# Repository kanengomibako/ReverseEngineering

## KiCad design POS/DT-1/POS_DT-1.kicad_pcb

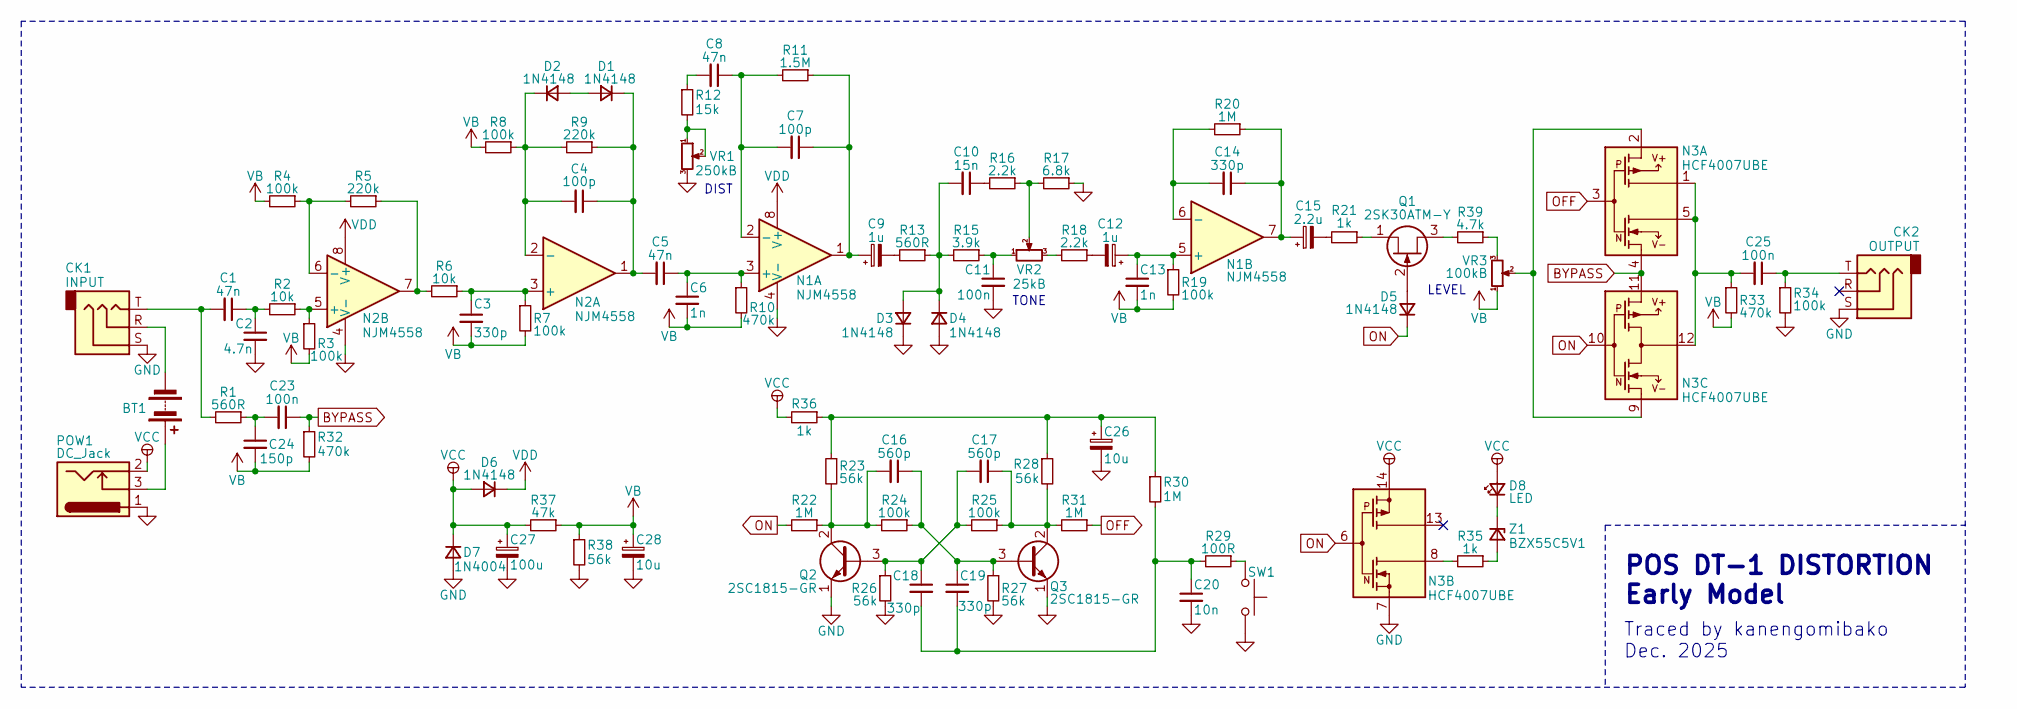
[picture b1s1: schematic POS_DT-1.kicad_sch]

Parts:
BT1: 006P; my_conn
C1, C5, C8: 47n; my_C_Rect1_P5.00mm
C2: 4.7n; my_C_Rect1_P5.00mm
C3, C14, C18, C19: 330p; my_C_Rect1_P5.00mm
C4, C7: 100p; my_C_Rect1_P5.00mm
C6, C13: 1n; my_C_Rect1_P5.00mm
C9, C12: 1u; my_C_D5.0mm_P2.50mm
C10: 15n; my_C_Rect1_P5.00mm
C11, C23, C25: 100n; my_C_Rect1_P5.00mm
C15: 2.2u; my_C_D5.0mm_P2.50mm
C16, C17: 560p; my_C_Rect1_P5.00mm
C20: 10n; my_C_Rect1_P5.00mm
C24: 150p; my_C_Rect1_P5.00mm
C26, C28: 10u; my_C_D5.0mm_P2.50mm
C27: 100u; my_C_D5.0mm_P2.50mm
CK1: INPUT; Audio_Jack_EX
CK2: OUTPUT; Audio_Jack_EX
D1, D2, D3, D4, D5, D6: 1N4148; my_D_P5.08mm_Horizontal
D7: 1N4004; my_D_P7.62mm
D8: LED; my_conn
N1, N2: NJM4558; DIP-8_W7.62mm
N3: HCF4007UBE; DIP-14_W7.62mm
POW1: DC_Jack; my_DC_Jack
Q1: 2SK30ATM-Y; TO-92_Inline_Wide
Q2, Q3: 2SC1815-GR; TO-92_Inline_Wide
R1: 560R; my_R_P5.08mm_Horizontal
R2, R6: 10k; my_R_P5.08mm_Horizontal
R3, R4, R7, R8, R19, R24, R25, R34: 100k; my_R_P5.08mm_Horizontal
R5, R9: 220k; my_R_P5.08mm_Horizontal
R10, R32, R33: 470k; my_R_P5.08mm_Horizontal
R11: 1.5M; my_R_P5.08mm_Horizontal
R12: 15k; my_R_P5.08mm_Horizontal
R13: 560R; my_R_P10mm_Horizontal
R15: 3.9k; my_R_P5.08mm_Horizontal
R16, R18: 2.2k; my_R_P5.08mm_Horizontal
R17: 6.8k; my_R_P5.08mm_Horizontal
R20, R30: 1M; my_R_P5.08mm_Horizontal
R21, R35, R36: 1k; my_R_P5.08mm_Horizontal
R22, R31: 1M; my_R_P10mm_Horizontal
R23: 56k; my_R_P10mm_Horizontal
R26, R27, R28, R38: 56k; my_R_P5.08mm_Horizontal
R29: 100R; my_R_P10mm_Horizontal
R37: 47k; my_R_P5.08mm_Horizontal
R39: 4.7k; my_R_P5.08mm_Horizontal
SW1: SW_Push; my_conn
VR1: 250kB; PinHeader_1x03_P2.54mm_Vertical
VR2: 25kB; PinHeader_1x03_P2.54mm_Vertical
VR3: 100kB; PinHeader_1x03_P2.54mm_Vertical
Z1: BZX55C5V1; my_D_P7.62mm

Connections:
BYPASS: C23.1, N3.4, N3.11, R32.1
GND: C2.2, C11.2, C20.2, C26.2, C27.2, C28.2, CK1.S, CK2.S, D3.1 (K), D4.2 (A), D7.2 (A), N1.4 (V-), N2.4 (V-), N3.7, POW1.1, Q2.1 (E), Q3.1 (E), R17.1, R26.2, R27.2, R34.2, R38.2, SW1.2, VR1.3
unnamed: BT1.1 (+), POW1.3
unnamed: BT1.2 (-), CK1.R
unnamed: C1.1, C2.1, R2.2
unnamed: C1.2, CK1.T, R1.2
unnamed: C7.1, C9.1, N1.1, R11.1
unnamed: C8.2, R12.1
unnamed: C9.2, R13.2
unnamed: C10.1, R16.2
unnamed: C11.1, R15.1, VR2.1
unnamed: C12.2, R18.1
unnamed: C14.1, C15.1, N1.7, R20.1
unnamed: C15.2, R21.2
unnamed: C18.2, C19.2, C20.1, R29.2, R30.2
unnamed: C23.2, C24.1, R1.1
unnamed: C25.1, CK2.T, R34.1
unnamed: C25.2, N3.1, N3.5, N3.12, R33.1
unnamed: C26.1, R23.1, R28.1, R30.1, R36.1
unnamed: D1.2 (A), D2.2 (A)
unnamed: C4.1, C5.2, D1.1 (K), N2.1, R9.1
unnamed: C4.2, D2.1 (K), N2.2 (-), R8.1, R9.2
unnamed: C10.2, D3.2 (A), D4.1 (K), R13.1, R15.2
unnamed: D5.2 (A), Q1.2 (G)
unnamed: D8.1 (K), Z1.1 (K)
unnamed: C5.1, C6.1, N1.3 (+), R10.1
unnamed: C7.2, C8.1, N1.2 (-), R11.2
unnamed: C12.1, C13.1, N1.5 (+), R19.1
unnamed: C14.2, N1.6 (-), R20.2
unnamed: N2.7, R5.1, R6.2
unnamed: C3.1, N2.3 (+), R6.1, R7.1
unnamed: N2.5 (+), R2.1, R3.1
unnamed: N2.6 (-), R4.1, R5.2
unnamed: N3.2, N3.9, VR3.2
unnamed: N3.8, R35.2
unnamed: Q1.3 (D), R39.2
unnamed: Q1.1 (S), R21.1
unnamed: C17.2, C18.1, Q2.3 (B), R25.2, R26.1
unnamed: C16.2, Q2.2 (C), R22.1, R23.2, R24.2
unnamed: C16.1, C19.1, Q3.3 (B), R24.1, R27.1
unnamed: C17.1, Q3.2 (C), R25.1, R28.2, R31.2
unnamed: R12.2, VR1.1, VR1.2
unnamed: R16.1, R17.2, VR2.2
unnamed: R18.2, VR2.3
unnamed: R29.1, SW1.1
unnamed: R39.1, VR3.3
unnamed: R35.1, Z1.2 (A)
OFF: N3.3, R31.1
ON: D5.1 (K), N3.6, N3.10, R22.2
VB: C3.2, C6.2, C13.2, C24.2, C28.1, R3.2, R4.2, R7.2, R8.2, R10.2, R19.2, R32.2, R33.2, R37.1, R38.1, VR3.1
VCC: C27.1, D6.2 (A), D7.1 (K), D8.2 (A), N3.14, POW1.2, R36.2, R37.2
VDD: D6.1 (K), N1.8 (V+), N2.8 (V+)

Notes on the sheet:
TONE
POS DT-1 DISTORTION Early Model
LEVEL
Traced by kanengomibako Dec. 2025
DIST

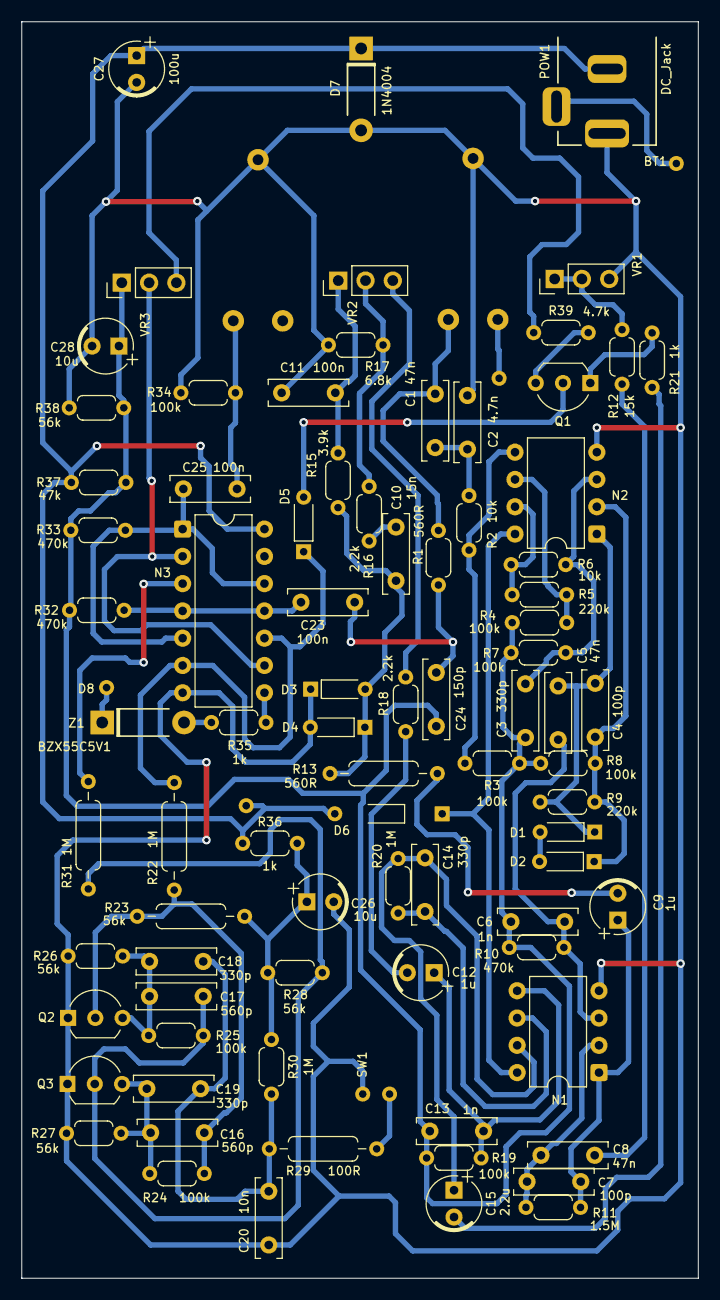
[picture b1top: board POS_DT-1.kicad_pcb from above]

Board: 2 copper layers, 63.0 x 117.0 mm, 87 parts (0 on the bottom side), 52 nets.

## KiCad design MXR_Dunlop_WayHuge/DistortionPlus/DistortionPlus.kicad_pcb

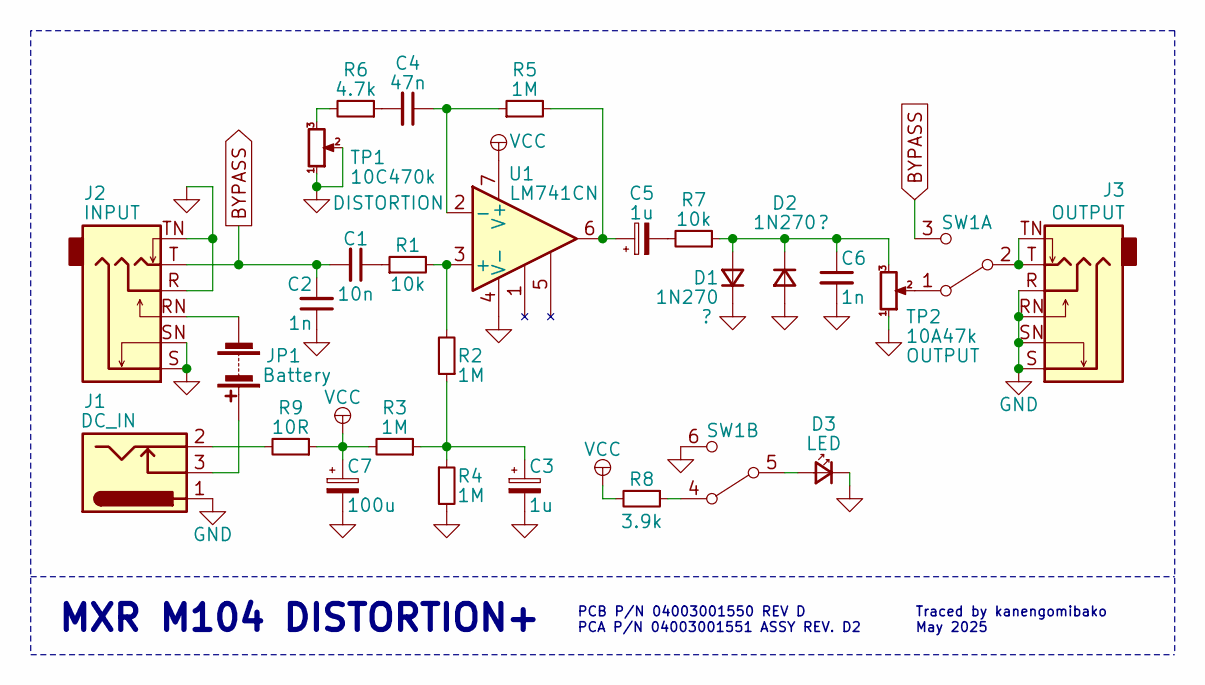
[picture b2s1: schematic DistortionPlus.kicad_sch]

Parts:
C1: 10n; my_C_Rect1_P5.00mm
C2, C6: 1n; my_C_Rect1_P5.00mm
C3, C5: 1u; CP_Radial_D5.0mm_P2.50mm
C4: 47n; my_C_Rect1_P5.00mm
C7: 100u; CP_Radial_D5.0mm_P2.50mm
D1, D2: 1N270; D_A-405_P10.16mm_Horizontal
D3: LED; LED_D3.0mm
J1: DC_IN; my_DC_Jack
J2: INPUT; Jack_6.35mm_Neutrik_NMJ6HCD2_Horizontal
J3: OUTPUT; Jack_6.35mm_Neutrik_NMJ6HCD2_Horizontal
JP1: Battery; my_conn
R1, R7: 10k; R_Axial_DIN0207_L6.3mm_D2.5mm_P10.16mm_Horizontal
R2, R3, R4, R5: 1M; R_Axial_DIN0207_L6.3mm_D2.5mm_P10.16mm_Horizontal
R6: 4.7k; R_Axial_DIN0207_L6.3mm_D2.5mm_P10.16mm_Horizontal
R8: 3.9k; R_Axial_DIN0207_L6.3mm_D2.5mm_P10.16mm_Horizontal
R9: 10R; R_Axial_DIN0207_L6.3mm_D2.5mm_P10.16mm_Horizontal
SW1: SW2; PinHeader_2x03_P2.54mm_Vertical
TP1: 10C470k; my_pot_5mm
TP2: 10A47k; my_pot_5mm
U1: LM741CN; DIP-8_W7.62mm_Socket

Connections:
BYPASS: C1.2, C2.2, J2.T, SW1.3 (C)
GND: C2.1, C3.2, C6.2, C7.2, D1.1 (K), D2.2 (A), D3.1 (K), J1.1, J2.R, J2.S, J2.SN, J2.TN, J3.R, J3.RN, J3.S, J3.SN, R4.2, SW1.6 (C), TP1.1, TP1.2, TP2.1, U1.4 (V-)
unnamed: C1.1, R1.1
unnamed: C3.1, R2.1, R3.1, R4.1
unnamed: C4.2, R6.1
unnamed: C5.1, R5.2, U1.6
unnamed: C5.2, R7.2
unnamed: C6.1, D1.2 (A), D2.1 (K), R7.1, TP2.3
unnamed: D3.2 (A), SW1.5 (B)
unnamed: J1.2, R9.2
unnamed: J1.3, JP1.1 (+)
unnamed: J2.RN, JP1.2 (-)
unnamed: R6.2, TP1.3
unnamed: SW1.1 (A), TP2.2
unnamed: J3.T, J3.TN, SW1.2 (B)
unnamed: R8.1, SW1.4 (A)
unnamed: R1.2, R2.2, U1.3 (+)
unnamed: C4.1, R5.1, U1.2 (-)
VCC: C7.1, R3.2, R8.2, R9.1, U1.7 (V+)

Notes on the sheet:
MXR M104 DISTORTION+
Traced by kanengomibako May 2025
PCB P/N 04003001550 REV D PCA P/N 04003001551 ASSY REV. D2

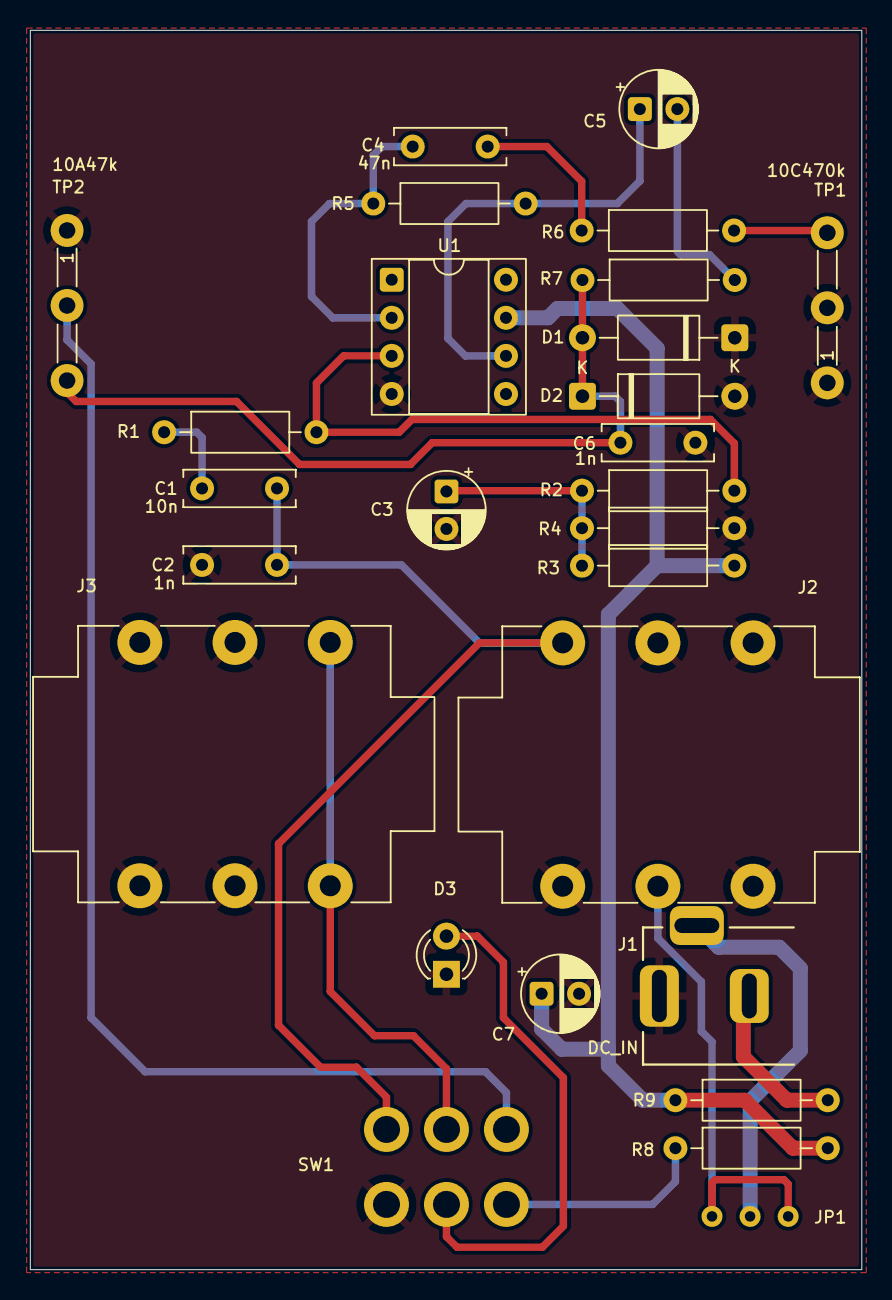
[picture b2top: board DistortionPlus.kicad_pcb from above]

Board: 2 copper layers, 55.5 x 82.7 mm, 27 parts (0 on the bottom side), 19 nets.

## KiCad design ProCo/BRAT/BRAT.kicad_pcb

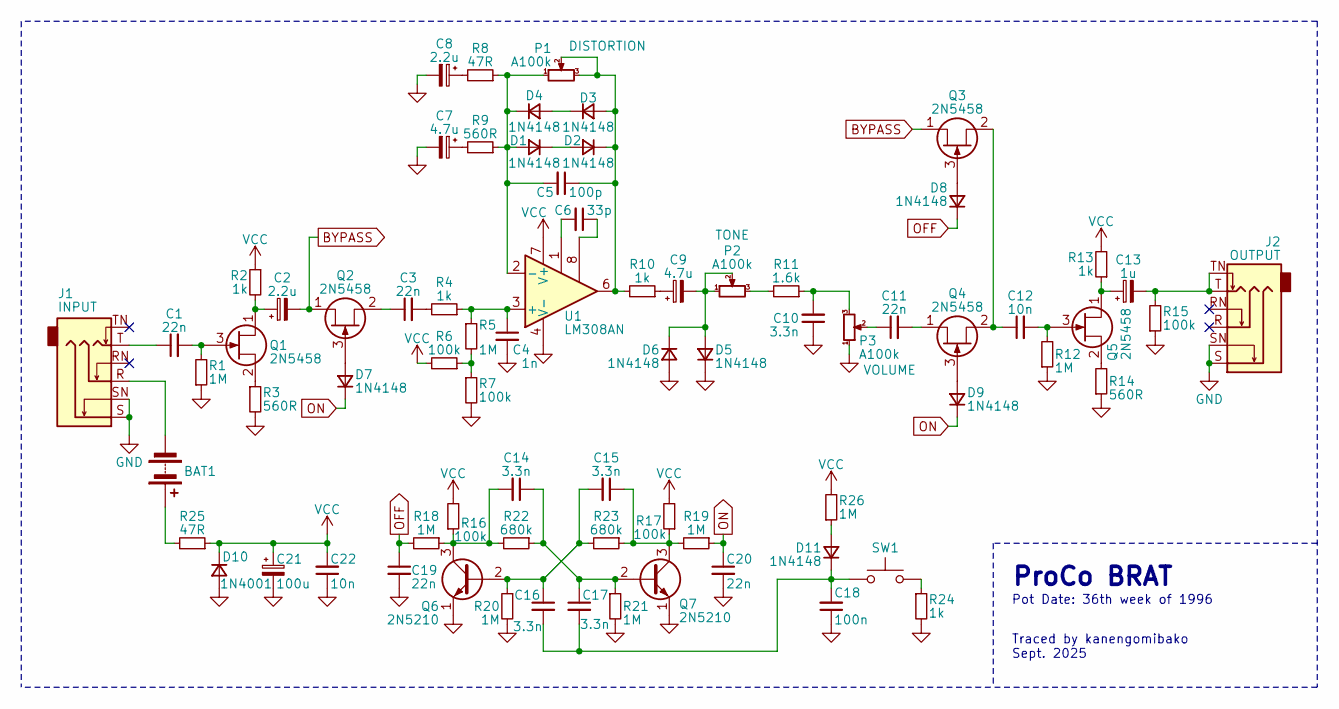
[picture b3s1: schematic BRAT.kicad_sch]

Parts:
BAT1: 9V; my_conn
C1, C3, C11, C19, C20: 22n; my_R_P8mm_Horizontal
C2, C8: 2.2u; CP_Radial_Tantal_D4.5mm_P5.00mm
C4: 1n; my_R_P8mm_Horizontal
C5: 100p; my_R_P8mm_Horizontal
C6: 33p; my_R_P8mm_Horizontal
C7, C9: 4.7u; CP_Radial_Tantal_D4.5mm_P5.00mm
C10, C14, C15, C16, C17: 3.3n; my_R_P8mm_Horizontal
C12, C22: 10n; my_R_P8mm_Horizontal
C13: 1u; CP_Radial_Tantal_D4.5mm_P5.00mm
C18: 100n; my_R_P8mm_Horizontal
C21: 100u; CP_Radial_Tantal_D4.5mm_P5.00mm
D1, D2, D3, D4, D5, D6, D7, D8, D9, D11: 1N4148; D_DO-35_SOD27_P10.16mm_Horizontal
D10: 1N4001; D_DO-35_SOD27_P10.16mm_Horizontal
J1: INPUT; my_Phone_Jack_Daier
J2: OUTPUT; my_Phone_Jack_Daier
P1, P2, P3: A100k; my_pot
Q1, Q2, Q3, Q4, Q5: 2N5458; TO-92L_Inline_Wide
Q6, Q7: 2N5210; TO-92L_Inline_Wide
R1, R5, R12, R18, R19, R20, R21, R26: 1M; my_R_P10mm_Horizontal
R2, R4, R10, R13, R24: 1k; my_R_P10mm_Horizontal
R3, R9, R14: 560R; my_R_P10mm_Horizontal
R6, R7, R15, R16, R17: 100k; my_R_P10mm_Horizontal
R8, R25: 47R; my_R_P10mm_Horizontal
R11: 1.6k; my_R_P10mm_Horizontal
R22, R23: 680k; my_R_P10mm_Horizontal
SW1: SW; my_conn
U1: LM308AN; DIP-8_W7.62mm

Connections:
BYPASS: C2.2, Q2.1 (D), Q3.1 (D)
GND: C4.2, C7.2, C8.2, C10.1, C18.1, C19.2, C20.2, C21.2, C22.1, D5.1 (K), D6.2 (A), D10.2 (A), J1.S, J1.SN, J2.S, J2.SN, P3.1, Q6.1 (E), Q7.1 (E), R1.1, R3.2, R7.2, R12.1, R14.1, R15.1, R20.2, R21.2, R24.2, U1.4 (V-)
unnamed: BAT1.1 (+), R25.2
unnamed: BAT1.2 (-), J1.R
unnamed: C1.1, J1.T
unnamed: C3.2, R4.2
unnamed: C6.1, U1.8
unnamed: C6.2, U1.1
unnamed: C7.1, R9.2
unnamed: C8.1, R8.2
unnamed: C9.1, R10.1
unnamed: C10.2, P3.3, R11.1
unnamed: C11.1, P3.2
unnamed: C13.2, J2.T, J2.TN, R15.2
unnamed: C5.2, D1.2 (A), D4.1 (K), P1.1, R8.1, R9.1, U1.2 (-)
unnamed: D1.1 (K), D2.2 (A)
unnamed: C5.1, D2.1 (K), D3.2 (A), P1.2, P1.3, R10.2, U1.6
unnamed: D3.1 (K), D4.2 (A)
unnamed: C9.2, D5.2 (A), D6.1 (K), P2.1, P2.2
unnamed: D7.2 (A), Q2.3 (G)
unnamed: D8.2 (A), Q3.3 (G)
unnamed: D9.2 (A), Q4.3 (G)
unnamed: D11.2 (A), R26.1
unnamed: C16.2, C17.2, C18.2, D11.1 (K), SW1.1
unnamed: P2.3, R11.2
unnamed: C2.1, Q1.1 (D), R2.2
unnamed: C1.2, Q1.3 (G), R1.2
unnamed: Q1.2 (S), R3.1
unnamed: C3.1, Q2.2 (S)
unnamed: C12.1, Q3.2 (S), Q4.2 (S)
unnamed: C11.2, Q4.1 (D)
unnamed: C13.1, Q5.1 (D), R13.1
unnamed: C12.2, Q5.3 (G), R12.2
unnamed: Q5.2 (S), R14.2
unnamed: C15.2, C16.1, Q6.2 (B), R20.1, R23.2
unnamed: C14.2, Q6.3 (C), R16.1, R18.1, R22.2
unnamed: C14.1, C17.1, Q7.2 (B), R21.1, R22.1
unnamed: C15.1, Q7.3 (C), R17.1, R19.2, R23.1
unnamed: R5.2, R6.1, R7.1
unnamed: R24.1, SW1.2
unnamed: C4.1, R4.1, R5.1, U1.3 (+)
OFF: C19.1, D8.1 (K), R18.2
ON: C20.1, D7.1 (K), D9.1 (K), R19.1
VCC: C21.1, C22.2, D10.1 (K), R2.1, R6.2, R13.2, R16.2, R17.2, R25.1, R26.2, U1.7 (V+)

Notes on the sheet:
ProCo BRAT
Pot Date: 36th week of 1996
Traced by kanengomibako Sept. 2025

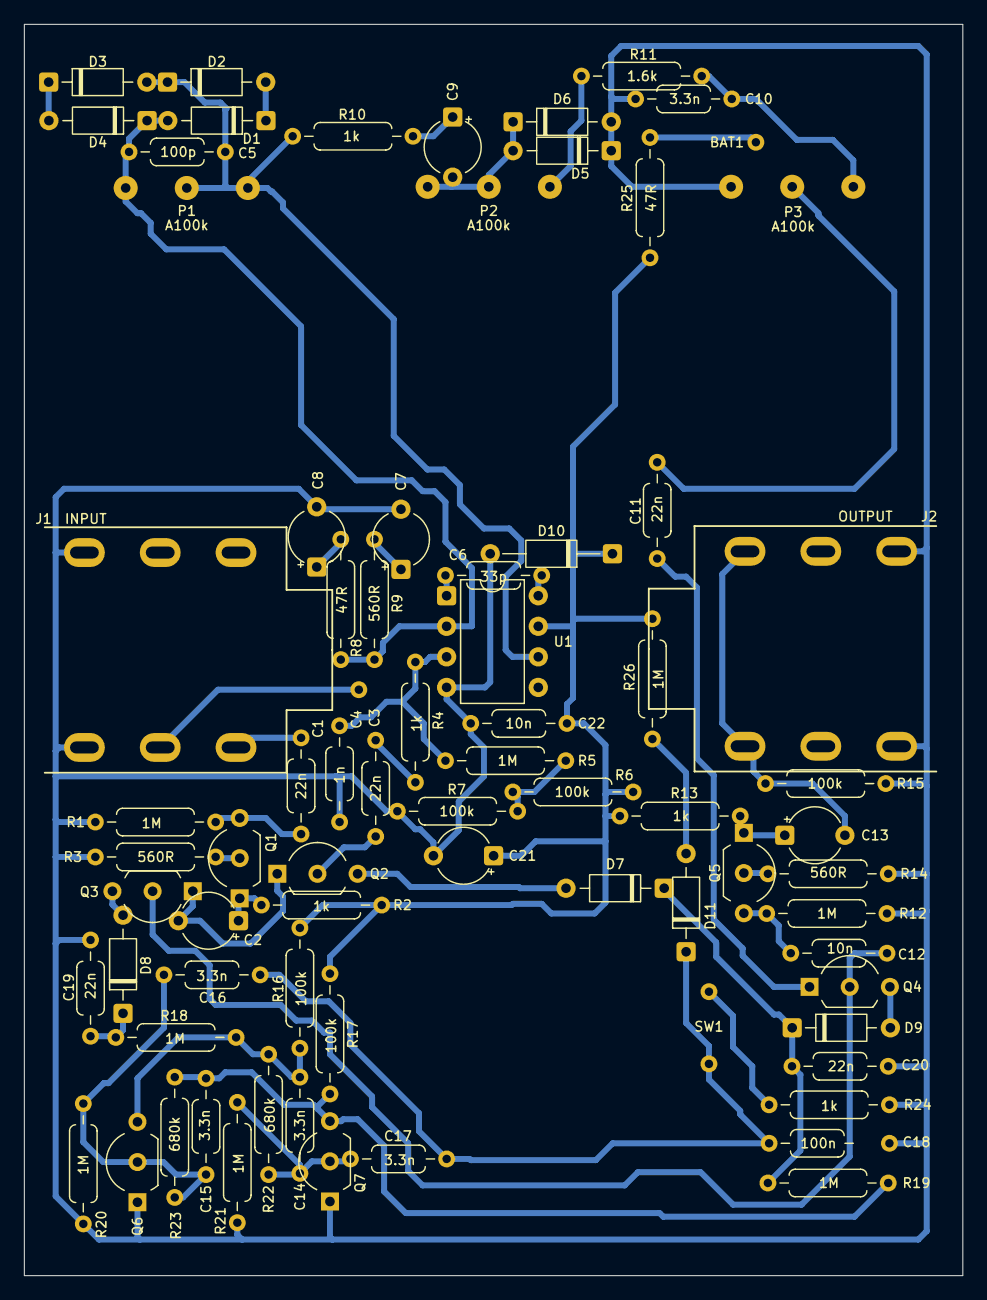
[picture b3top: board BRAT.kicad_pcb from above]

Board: 2 copper layers, 78.0 x 104.0 mm, 74 parts (0 on the bottom side), 44 nets.

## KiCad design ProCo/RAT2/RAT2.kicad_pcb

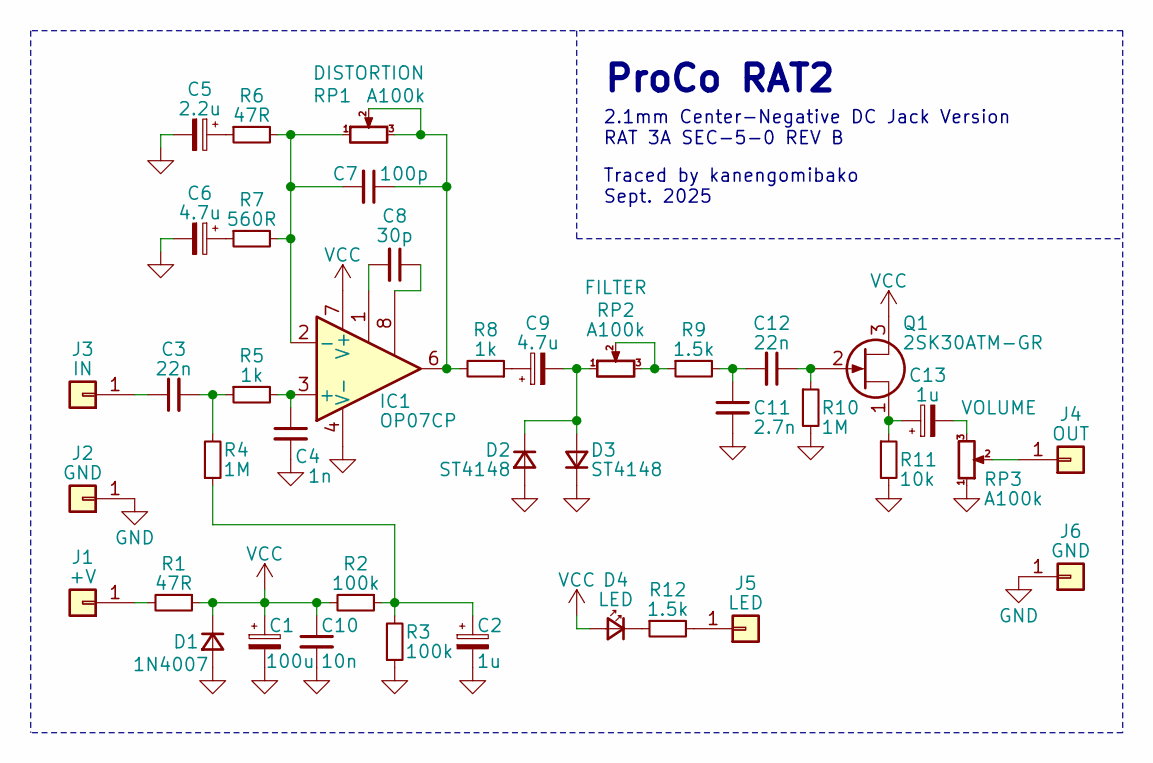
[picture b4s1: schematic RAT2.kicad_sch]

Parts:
C1: 100u; CP_Radial_D5.0mm_P2.50mm
C2, C13: 1u; CP_Radial_D5.0mm_P2.50mm
C3, C12: 22n; C_Rect_L7.0mm_W2.5mm_P5.00mm
C4: 1n; C_Rect_L7.0mm_W2.5mm_P5.00mm
C5: 2.2u; CP_Radial_D5.0mm_P2.50mm
C6, C9: 4.7u; CP_Radial_D5.0mm_P2.50mm
C7: 100p; C_Rect_L7.0mm_W2.5mm_P5.00mm
C8: 30p; C_Rect_L7.0mm_W2.5mm_P5.00mm
C10: 10n; C_Rect_L7.0mm_W2.5mm_P5.00mm
C11: 2.7n; C_Rect_L7.0mm_W2.5mm_P5.00mm
D1: 1N4007; D_DO-41_SOD81_P10.16mm_Horizontal
D2, D3: ST4148; D_DO-41_SOD81_P10.16mm_Horizontal
D4: LED; LED_D5.0mm
IC1: OP07CP; DIP-8_W7.62mm
J1: +V; PinHeader_1x01_P2.54mm_Vertical
J2, J6: GND; PinHeader_1x01_P2.54mm_Vertical
J3: IN; PinHeader_1x01_P2.54mm_Vertical
J4: OUT; PinHeader_1x01_P2.54mm_Vertical
J5: LED; PinHeader_1x01_P2.54mm_Vertical
Q1: 2SK30ATM-GR; TO-92_Inline_Wide
R1, R6: 47R; R_Axial_DIN0207_L6.3mm_D2.5mm_P10.16mm_Horizontal
R2, R3: 100k; R_Axial_DIN0207_L6.3mm_D2.5mm_P10.16mm_Horizontal
R4, R10: 1M; R_Axial_DIN0207_L6.3mm_D2.5mm_P10.16mm_Horizontal
R5, R8: 1k; R_Axial_DIN0207_L6.3mm_D2.5mm_P10.16mm_Horizontal
R7: 560R; R_Axial_DIN0207_L6.3mm_D2.5mm_P10.16mm_Horizontal
R9, R12: 1.5k; R_Axial_DIN0207_L6.3mm_D2.5mm_P10.16mm_Horizontal
R11: 10k; R_Axial_DIN0207_L6.3mm_D2.5mm_P10.16mm_Horizontal
RP1, RP2, RP3: A100k; Potentiometer_Omeg_PC16BU_Vertical

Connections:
GND: C1.2, C2.2, C4.2, C5.2, C6.2, C10.2, C11.2, D1.2 (A), D2.2 (A), D3.1 (K), IC1.4 (V-), J2.1, J6.1, R3.1, R10.2, R11.2, RP3.1
unnamed: C2.1, R2.1, R3.2, R4.1
unnamed: C3.2, R4.2, R5.1
unnamed: C5.1, R6.1
unnamed: C6.1, R7.1
unnamed: C7.1, IC1.6, R8.2, RP1.2, RP1.3
unnamed: C8.1, IC1.8
unnamed: C8.2, IC1.1
unnamed: C9.1, R8.1
unnamed: C11.1, C12.2, R9.2
unnamed: C13.2, RP3.3
unnamed: C9.2, D2.1 (K), D3.2 (A), RP2.1
unnamed: D4.1 (K), R12.1
unnamed: C4.1, IC1.3 (+), R5.2
unnamed: C7.2, IC1.2 (-), R6.2, R7.2, RP1.1
unnamed: J1.1, R1.2
unnamed: C3.1, J3.1
unnamed: J4.1, RP3.2
unnamed: J5.1, R12.2
unnamed: C12.1, Q1.2 (G), R10.1
unnamed: C13.1, Q1.1 (S), R11.1
unnamed: R9.1, RP2.2, RP2.3
VCC: C1.1, C10.1, D1.1 (K), D4.2 (A), IC1.7 (V+), Q1.3 (D), R1.1, R2.2

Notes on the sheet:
Traced by kanengomibako Sept. 2025
2.1mm Center-Negative DC Jack Version RAT 3A SEC-5-0 REV B
ProCo RAT2

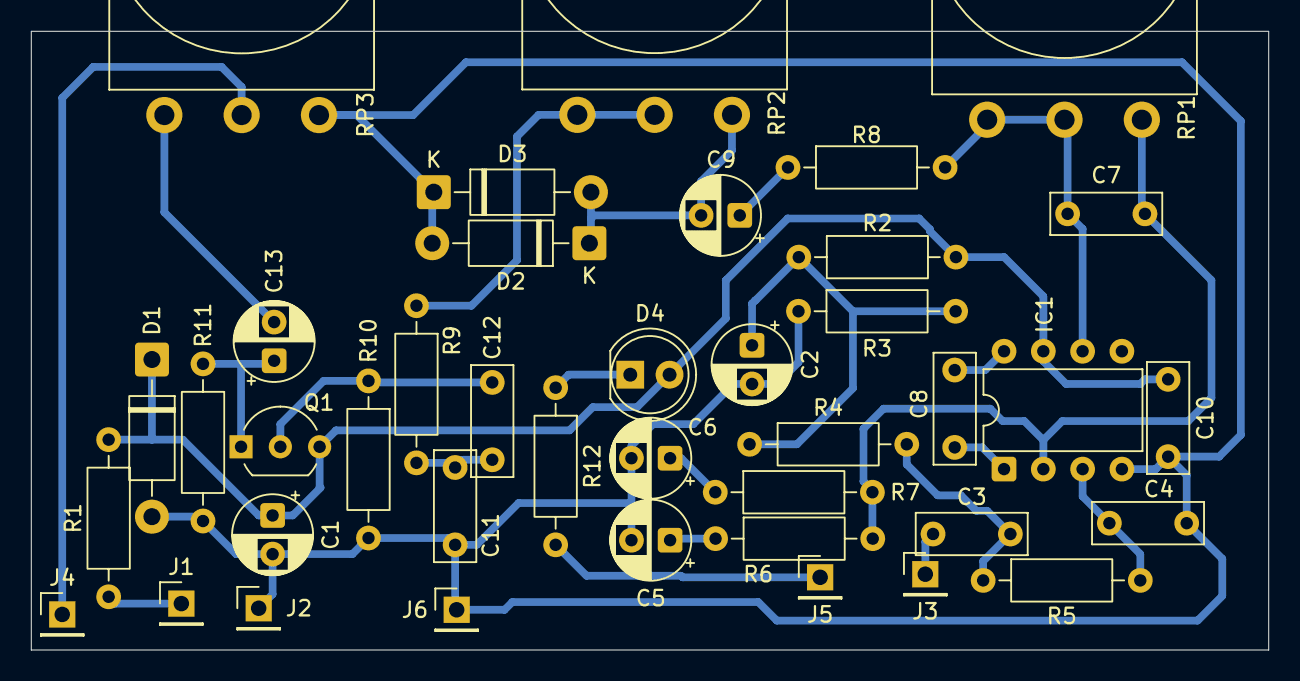
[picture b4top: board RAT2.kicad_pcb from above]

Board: 2 copper layers, 80.0 x 40.0 mm, 40 parts (0 on the bottom side), 23 nets.

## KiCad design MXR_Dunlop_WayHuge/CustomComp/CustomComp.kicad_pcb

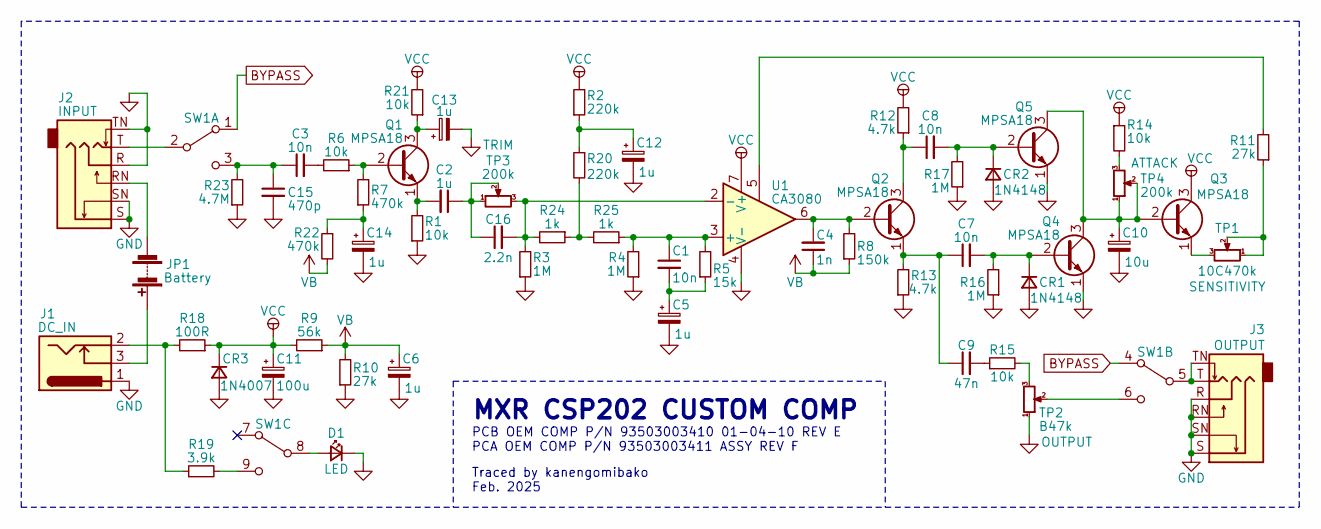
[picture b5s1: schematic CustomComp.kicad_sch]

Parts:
C1, C3, C7, C8: 10n; C_Disc_D4.3mm_W1.9mm_P5.00mm
C2: 1u; C_Disc_D4.3mm_W1.9mm_P5.00mm
C4: 1n; C_Disc_D4.3mm_W1.9mm_P5.00mm
C5, C6, C12, C14: 1u; CP_Radial_D5.0mm_P2.00mm
C9: 47n; C_Disc_D4.3mm_W1.9mm_P5.00mm
C10: 10u; CP_Radial_D5.0mm_P2.00mm
C11: 100u; CP_Radial_D5.0mm_P2.50mm
C13: 1u; CP_Radial_D4.0mm_P2.00mm
C15: 470p; C_Disc_D4.3mm_W1.9mm_P5.00mm
C16: 2.2n; C_Disc_D4.3mm_W1.9mm_P5.00mm
CR1, CR2: 1N4148; D_DO-35_SOD27_P10.16mm_Horizontal
CR3: 1N4007; D_DO-35_SOD27_P10.16mm_Horizontal
D1: LED; LED_D5.0mm
J1: DC_IN; my_DC_Jack
J2: INPUT; Jack_6.35mm_Neutrik_NMJ6HCD2_Horizontal
J3: OUTPUT; Jack_6.35mm_Neutrik_NMJ6HCD2_Horizontal
JP1: Battery; my_conn
Q1, Q2, Q3, Q4, Q5: MPSA18; TO-92_Wide
R1, R6, R14, R15, R21: 10k; R_Axial_DIN0207_L6.3mm_D2.5mm_P10.16mm_Horizontal
R2, R20: 220k; R_Axial_DIN0207_L6.3mm_D2.5mm_P10.16mm_Horizontal
R3, R4, R16, R17: 1M; R_Axial_DIN0207_L6.3mm_D2.5mm_P10.16mm_Horizontal
R5: 15k; R_Axial_DIN0207_L6.3mm_D2.5mm_P10.16mm_Horizontal
R7, R22: 470k; R_Axial_DIN0207_L6.3mm_D2.5mm_P10.16mm_Horizontal
R8: 150k; R_Axial_DIN0207_L6.3mm_D2.5mm_P10.16mm_Horizontal
R9: 56k; R_Axial_DIN0207_L6.3mm_D2.5mm_P10.16mm_Horizontal
R10, R11: 27k; R_Axial_DIN0207_L6.3mm_D2.5mm_P10.16mm_Horizontal
R12, R13: 4.7k; R_Axial_DIN0207_L6.3mm_D2.5mm_P10.16mm_Horizontal
R18: 100R; R_Axial_DIN0207_L6.3mm_D2.5mm_P10.16mm_Horizontal
R19: 3.9k; R_Axial_DIN0207_L6.3mm_D2.5mm_P10.16mm_Horizontal
R23: 4.7M; R_Axial_DIN0207_L6.3mm_D2.5mm_P10.16mm_Horizontal
R24, R25: 1k; R_Axial_DIN0207_L6.3mm_D2.5mm_P10.16mm_Horizontal
SW1: SW_3PDT; my_sw_3pdt
TP1: 10C470k; my_pot_5mm
TP2: B47k; my_pot_5mm
TP3, TP4: 200k; Potentiometer_ACP_CA9-V10_Vertical_Hole
U1: CA3080; DIP-8_W7.62mm

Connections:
BYPASS: SW1.1 (A), SW1.4 (A)
GND: C5.2, C6.2, C10.2, C11.2, C12.2, C13.2, C14.2, C15.2, CR1.2 (A), CR2.2 (A), CR3.2 (A), D1.1 (K), J1.1, J2.R, J2.S, J2.SN, J2.TN, J3.R, J3.RN, J3.S, J3.SN, Q4.1 (E), Q5.1 (E), R1.1, R3.1, R4.1, R10.1, R13.1, R16.1, R17.1, R23.1, TP2.1, U1.4 (V-)
unnamed: C1.2, C5.1, R5.1
unnamed: C3.2, R6.2
unnamed: C9.2, R15.1
unnamed: C12.1, R2.1, R20.1
unnamed: C14.1, R7.1, R22.1
unnamed: C2.1, C16.1, TP3.1, TP3.2
unnamed: C7.2, CR1.1 (K), Q4.2 (B), R16.2
unnamed: C8.2, CR2.1 (K), Q5.2 (B), R17.2
unnamed: D1.2 (A), SW1.8 (B)
unnamed: J1.2, R18.2, R19.1
unnamed: J1.3, JP1.1 (+)
unnamed: J2.RN, JP1.2 (-)
unnamed: Q1.2 (B), R6.1, R7.2
unnamed: C13.1, Q1.3 (C), R21.1
unnamed: C2.2, Q1.1 (E), R1.2
unnamed: C4.2, Q2.2 (B), R8.2, U1.6
unnamed: C8.1, Q2.3 (C), R12.1
unnamed: C7.1, C9.1, Q2.1 (E), R13.2
unnamed: C10.1, Q3.2 (B), Q4.3 (C), Q5.3 (C), TP4.1, TP4.2
unnamed: Q3.1 (E), TP1.3
unnamed: R11.1, TP1.1, TP1.2
unnamed: R11.2, U1.5
unnamed: R14.2, TP4.3
unnamed: R15.2, TP2.3
unnamed: R20.2, R24.1, R25.2
unnamed: J2.T, SW1.2 (B)
unnamed: C3.1, C15.1, R23.2, SW1.3 (C)
unnamed: J3.T, J3.TN, SW1.5 (B)
unnamed: SW1.6 (C), TP2.2
unnamed: R19.2, SW1.9 (C)
unnamed: C1.1, R4.2, R5.2, R25.1, U1.3 (+)
unnamed: C16.2, R3.2, R24.2, TP3.3, U1.2 (-)
VB: C4.1, C6.1, R8.1, R9.1, R10.2, R22.2
VCC: C11.1, CR3.1 (K), Q3.3 (C), R2.2, R9.2, R12.2, R14.1, R18.1, R21.2, U1.7 (V+)

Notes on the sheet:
MXR CSP202 CUSTOM COMP
Traced by kanengomibako Feb. 2025
PCB OEM COMP P/N 93503003410 01-04-10 REV E PCA OEM COMP P/N 93503003411 ASSY REV F

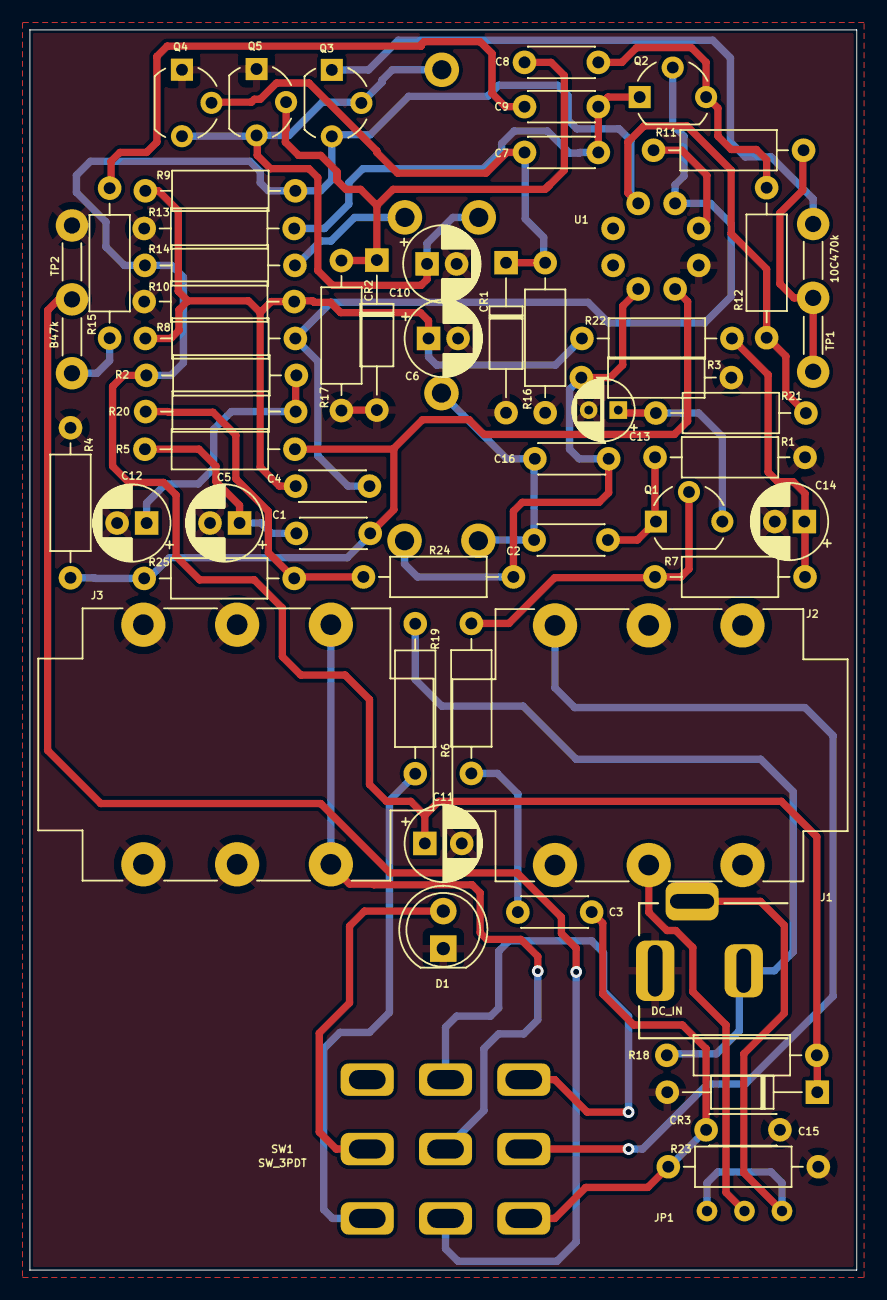
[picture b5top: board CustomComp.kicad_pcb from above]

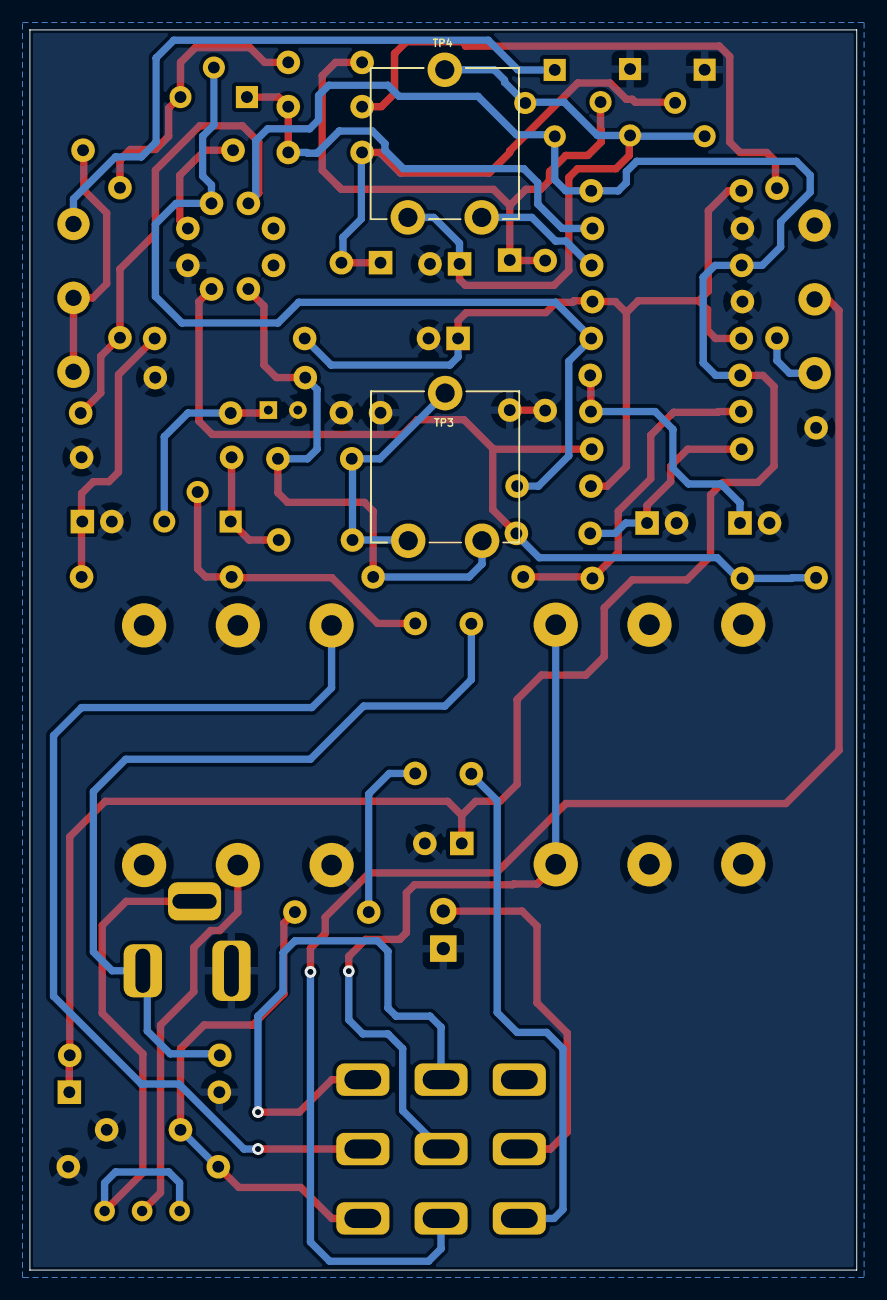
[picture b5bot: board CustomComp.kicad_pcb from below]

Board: 11 copper layers, 56.0 x 84.0 mm, 60 parts (2 on the bottom side), 36 nets.

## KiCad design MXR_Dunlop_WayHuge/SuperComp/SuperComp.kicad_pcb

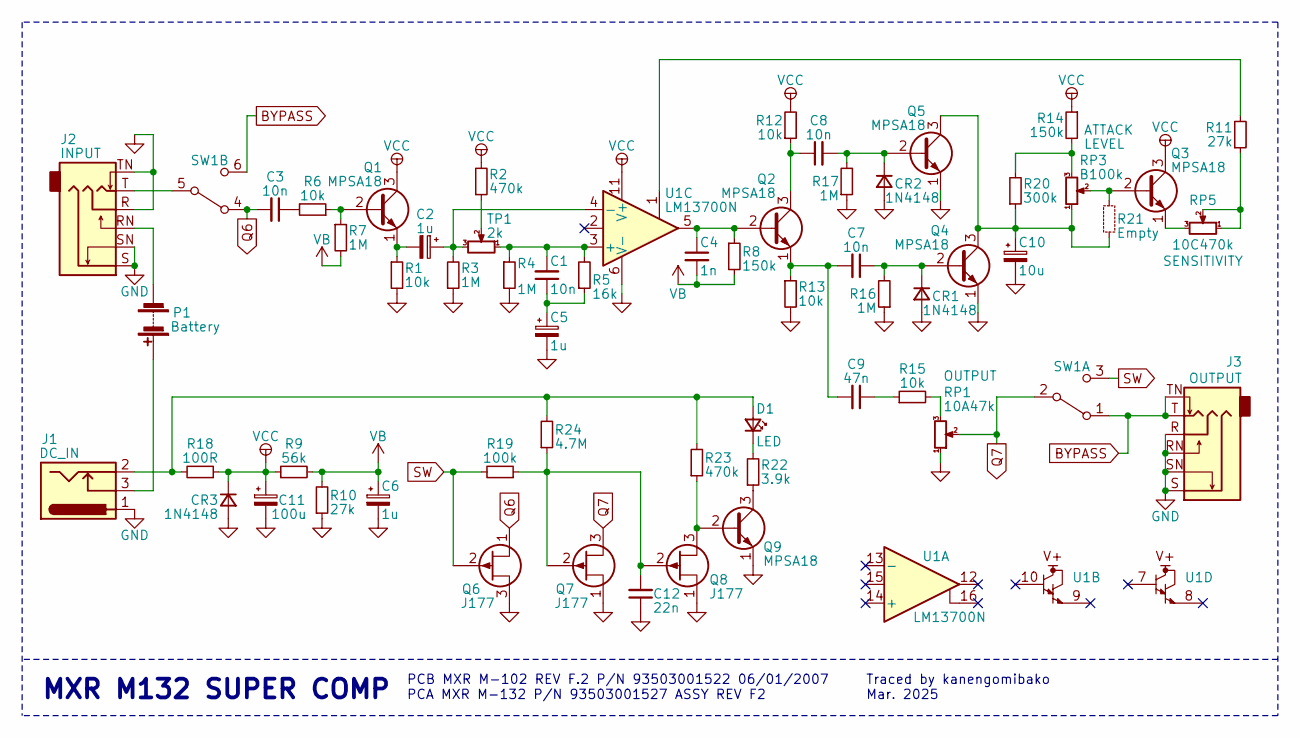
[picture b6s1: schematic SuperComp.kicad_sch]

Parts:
C1, C3, C7, C8: 10n; C_Disc_D4.3mm_W1.9mm_P5.00mm
C2, C5, C6: 1u; CP_Radial_D5.0mm_P2.50mm
C4: 1n; C_Disc_D4.3mm_W1.9mm_P5.00mm
C9: 47n; C_Disc_D4.3mm_W1.9mm_P5.00mm
C10: 10u; CP_Radial_D5.0mm_P2.50mm
C11: 100u; CP_Radial_D5.0mm_P2.50mm
C12: 22n; C_Disc_D4.3mm_W1.9mm_P5.00mm
CR1, CR2, CR3: 1N4148; D_DO-35_SOD27_P10.16mm_Horizontal
D1: LED; LED_D5.0mm
J1: DC_IN; my_DC_Jack
J2: INPUT; Jack_6.35mm_Neutrik_NMJ6HCD2_Horizontal
J3: OUTPUT; Jack_6.35mm_Neutrik_NMJ6HCD2_Horizontal
P1: Battery; my_conn
Q1, Q2, Q3, Q4, Q5, Q9: MPSA18; TO-92_Wide
Q6, Q7, Q8: J177; TO-92_Wide
R1, R6, R12, R13, R15: 10k; R_Axial_DIN0207_L6.3mm_D2.5mm_P10.16mm_Horizontal
R2, R23: 470k; R_Axial_DIN0207_L6.3mm_D2.5mm_P10.16mm_Horizontal
R3, R4, R7, R16, R17: 1M; R_Axial_DIN0207_L6.3mm_D2.5mm_P10.16mm_Horizontal
R5: 16k; R_Axial_DIN0207_L6.3mm_D2.5mm_P10.16mm_Horizontal
R8, R14: 150k; R_Axial_DIN0207_L6.3mm_D2.5mm_P10.16mm_Horizontal
R9: 56k; R_Axial_DIN0207_L6.3mm_D2.5mm_P10.16mm_Horizontal
R10, R11: 27k; R_Axial_DIN0207_L6.3mm_D2.5mm_P10.16mm_Horizontal
R18: 100R; R_Axial_DIN0207_L6.3mm_D2.5mm_P10.16mm_Horizontal
R19: 100k; R_Axial_DIN0207_L6.3mm_D2.5mm_P10.16mm_Horizontal
R20: 300k; R_Axial_DIN0207_L6.3mm_D2.5mm_P10.16mm_Horizontal
R21: Empty; R_Axial_DIN0207_L6.3mm_D2.5mm_P10.16mm_Horizontal
R22: 3.9k; R_Axial_DIN0207_L6.3mm_D2.5mm_P10.16mm_Horizontal
R24: 4.7M; R_Axial_DIN0207_L6.3mm_D2.5mm_P10.16mm_Horizontal
RP1: 10A47k; my_pot_5mm
RP3: B100k; my_pot_5mm
RP5: 10C470k; my_pot_5mm
SW1: SW1; PinHeader_2x03_P2.54mm_Vertical
TP1: 2k; Potentiometer_ACP_CA9-V10_Vertical_Hole
U1: LM13700N; DIP-16_W7.62mm

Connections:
BYPASS: J3.T, J3.TN, SW1.1 (A), SW1.6 (C)
GND: C5.2, C6.2, C10.2, C11.2, C12.1, CR1.2 (A), CR2.2 (A), CR3.2 (A), J1.1, J2.R, J2.S, J2.SN, J2.TN, J3.R, J3.RN, J3.S, J3.SN, Q4.1 (E), Q5.1 (E), Q6.3 (D), Q7.1 (S), Q8.1 (S), Q9.1 (E), R1.2, R3.1, R4.2, R10.1, R13.2, R16.1, R17.1, RP1.1, U1.6 (V-); also elsewhere on the board
unnamed: C1.1, C5.1, R5.1
unnamed: C3.1, R6.2
unnamed: C9.1, R15.1
unnamed: C7.1, CR1.1 (K), Q4.2 (B), R16.2
unnamed: C8.2, CR2.1 (K), Q5.2 (B), R17.2
unnamed: D1.2 (A), J1.2, R18.2, R23.2, R24.2
unnamed: D1.1 (K), R22.2
unnamed: J1.3, P1.1 (+)
unnamed: J2.RN, P1.2 (-)
unnamed: Q1.2 (B), R6.1, R7.1
unnamed: C2.2, Q1.1 (E), R1.1
unnamed: C4.1, Q2.2 (B), R8.1, U1.5
unnamed: C8.1, Q2.3 (C), R12.1
unnamed: C7.2, C9.2, Q2.1 (E), R13.1
unnamed: Q3.2 (B), R21.2, RP3.2
unnamed 17: Q3.1 (E), RP5.3; also elsewhere on the board
unnamed: C10.1, Q4.3 (C), Q5.3 (C), R20.1, R21.1, RP3.1
unnamed: C12.2, Q7.2 (G), Q8.2 (G), R19.1, R24.1
unnamed: Q8.3 (D), Q9.2 (B), R23.1
unnamed: Q9.3 (C), R22.1
unnamed: R2.1, TP1.2
unnamed 23: R11.1, RP5.1, RP5.2; also elsewhere on the board
unnamed: R11.2, U1.1
unnamed: R14.2, R20.2, RP3.3
unnamed 26: R15.2, RP1.3; also elsewhere on the board
unnamed: J2.T, SW1.5 (B)
unnamed: C1.2, R4.1, R5.2, TP1.1, U1.3 (+)
unnamed: C2.1, R3.2, TP1.3, U1.4 (-)
Q6: C3.2, Q6.1 (S), SW1.4 (A)
Q7: Q7.3 (D), RP1.2, SW1.2 (B); also elsewhere on the board
SW: Q6.2 (G), R19.2, SW1.3 (C)
VB: C4.2, C6.1, R7.2, R8.2, R9.2, R10.2
VCC: C11.1, CR3.1 (K), Q1.3 (C), Q3.3 (C), R2.2, R9.1, R12.2, R14.1, R18.1, U1.11 (V+)

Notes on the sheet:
MXR M132 SUPER COMP
Traced by kanengomibako Mar. 2025
PCB MXR M-102 REV F.2 P/N 93503001522 06/01/2007 PCA MXR M-132 P/N 93503001527 ASSY REV F2
